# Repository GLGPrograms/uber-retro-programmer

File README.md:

# ÜRP - Über Retro Programmer

An EEPROM programmer for retro playing.
- Can dump most parallel (EE)PROM memories, like 27xxx and 28xxx.
- Supports RW operations of most 28Cxxx EEPROM.
- Suppport may be extended to flash memories up to 1MiB.

## What's inside

This repository is organized as follows
```
ÜRP
 |__ hw          --> KiCAD schematics
 |   |__ gerbers  -> fabrication files (gerbers)
 |   |__ urp.pdf  -> PDF schematic
 |   |__ urp.pro  -> KiCAD project
 |__ fw          --> source code for atmega 328
 |__ sw          --> source code for PC Command Line Interface
 |__ docs        --> files related to documentation
```

After clone, init submodules:
```
git submodule update
````

## PCB Assembly

|Designator      | Description                  | Notes                   |
|----------------|------------------------------|-------------------------|
|C1-C5           | capacitor ceramic 100n P5.08 |                         |
|C6-C7           | capacitor ceramic 22p P2.54  |                         |
|R1              | resistor 10k                 |                         |
|R2-R4           | resistor 330                 |                         |
|Y1              | crystal 16M                  |                         |
|SW1             | Tactile switch               |                         |
|D1-D3           | LED 5mm                      | e.g. green, yellow, red |
|U1              | microcontroller ATMega 328   |                         |
|U2 U3           | shift register 74HC595       |                         |
|JP1-JP5         | 3-pin header 2.54            | EEPROM size selection   |
|J1              | 6-pin header 2.54            |                         |
|J2              | ZIF socket 32 pin wide       |                         |
|J3              | 2-pin header 2.54            | optional                |
|R5              | resistor 10k                 | optional                |
|R6              | resistor 3k3                 | optional                |
|Q1              | PMOS (2N7002)                | optional                |

**Warning:** When Q1 is not mounted, JP7 must be shorted.

## How to compile and load firmware

1. Mount atmega328 on an Arduino UNO board or equivalent. If is a fresh chip, you must load an Arduino compatible bootloader (e.g. optiboot).

1. Compile firmware in `fw` folder using the makefile. Change `/dev/ttyXYZ123` with the correct serial port (e.g. /dev/ttyUSB0);

```
cd fw
make
make program AVRDUDEPORT=/dev/ttyXYZ123
```

1. Move the atmega328 on the ÜRP.

### How to use EEPROM size selection pins

Jumpers JP1-JP6 must be placed according to memory size and technology.
Each jumper has three positions, 1 (green), 2 (red) or unmounted (gray).
Please refer to the following tables for correct placement.

#### EEPROM pinout

#### EPROM pinout

**Notes:**
- EPROM support is read only;
- Most EPROM have VPP on JP2. Datasheet recommends to put VPP=VCC during reading operations. I often keep JP2 in position (1) and make read operations starting from 32768 (A15=VCC).

## How to compile CLI

    cd sw
    make

### CLI options

    Usage: ./serprog options

    -r --read arg                read the content of eeprom in file. Must specify size and addr
    -w --write arg               write the content of file in eeprom, then verify. Must specify addr
    -v --verify arg              verify the content of the file with the eeprom. Must specify addr
    -n --noverify                skip verification after write
    -e --erase                   erase the eeprom (by software, i.e. write FF)
    -V --verbose [arg]           set verbosity level to arg (0 low, 7 high)
    -s --size arg                set reading size
    -a --addr arg                set starting address (default 0)
    -d --device arg              set serial device (default /dev/ttyUSB0)
    -U --unlock                  unlock before
    -P --lock                    lock after
    -h --help                    print this help

#### Read a 28C256 EEPROM (8KiB)

    ./serprog --device /dev/ttyACMx --read dump.bin -s 8192

#### Write a binary image

    ./serprog --device /dev/ttyACMx --write dump.bin

If the EEPROM fails verify, SDP (Software Data Protection) may be on.
Try disabling.

    ./serprog --device /dev/ttyACMx -U --write dump.bin

In both cases, size is deducted from the binary image.

#### Manually verify against a binary image

    ./serprog --device /dev/ttyACMx --verify dump.bin

Size is deducted from the binary image.

#### Protect EEPROM with SDP

    ./serprog --device /dev/ttyACMx -P

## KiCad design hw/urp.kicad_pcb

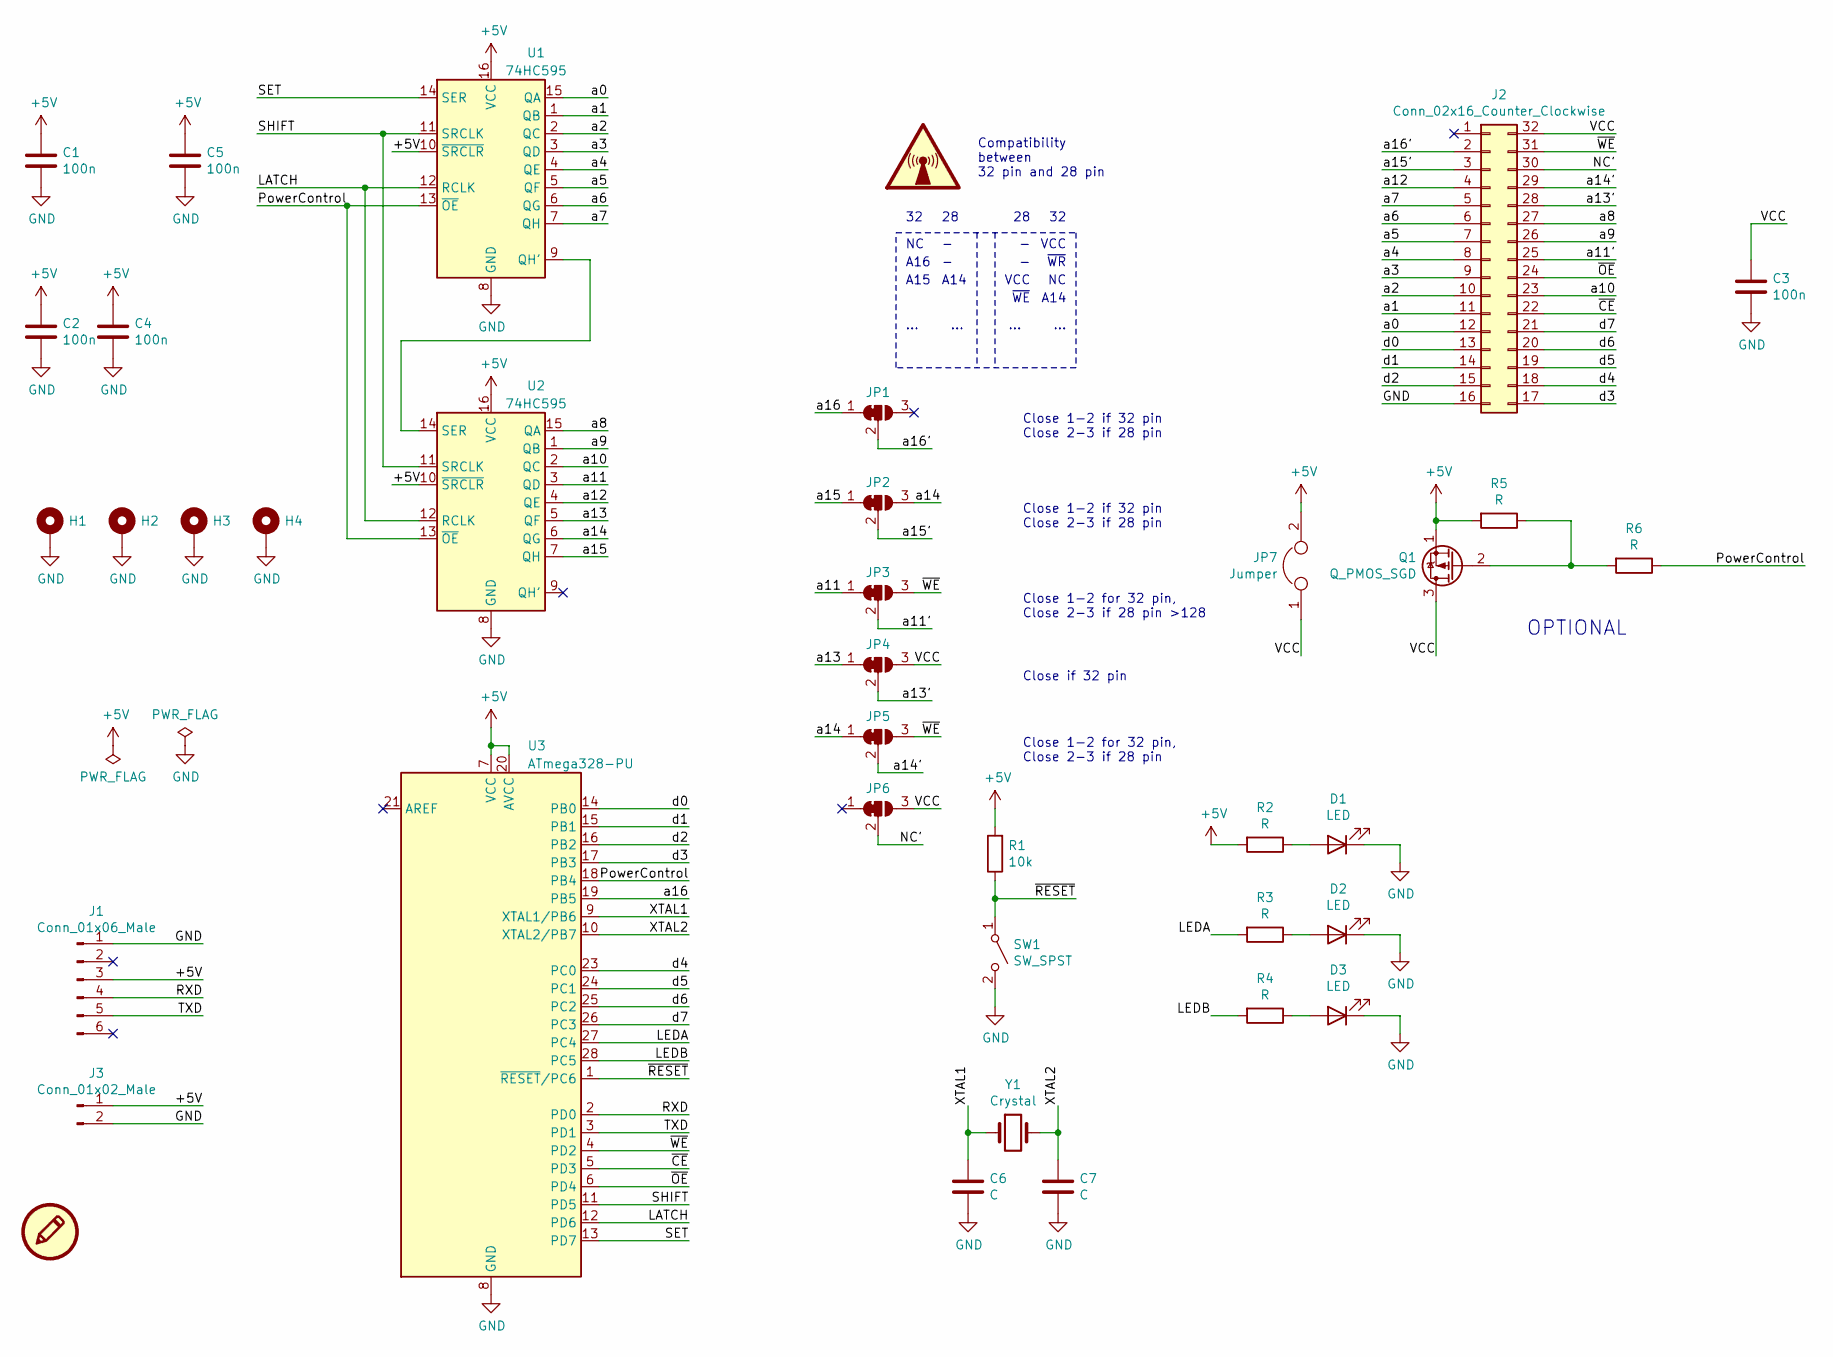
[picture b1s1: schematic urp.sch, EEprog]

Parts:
C1, C2, C3, C4, C5: 100n; C_Disc_D4.7mm_W2.5mm_P5.00mm
C6, C7: C; C_Disc_D3.0mm_W1.6mm_P2.50mm
D1, D2, D3: LED; LED_D5.0mm
H1, H2, H3, H4: MountingHole_Pad; MountingHole_3.2mm_M3_Pad
J1: Conn_01x06_Male; PinHeader_1x06_P2.54mm_Vertical
J2: Conn_02x16_Counter_Clockwise; DIP_Socket-32_W11.9_W12.7_W15.24_W17.78_W18.5_3M_232-1285-0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
J3: Conn_01x02_Male; Molex_KK-254_AE-6410-02A_1x02_P2.54mm_Vertical
JP1, JP2, JP3, JP4, JP5, JP6: SolderJumper_3_Bridged12; PinHeader_1x03_P2.54mm_Vertical
JP7: Jumper; SolderJumper-2_P1.3mm_Open_TrianglePad1.0x1.5mm
Q1: Q_PMOS_SGD; TO-92_Inline
R1: 10k; R_Axial_DIN0204_L3.6mm_D1.6mm_P7.62mm_Horizontal
R2, R3, R4, R5, R6: R; R_Axial_DIN0204_L3.6mm_D1.6mm_P7.62mm_Horizontal
SW1: SW_SPST; SW_PUSH_6mm_H4.3mm
SYM1: GraphicSymbol
U1, U2: 74HC595; DIP-16_W7.62mm_Socket_LongPads
U3: ATmega328-PU; DIP-28_W7.62mm
Y1: Crystal; Crystal_HC49-4H_Vertical

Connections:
+5V: C1.1, C2.1, C4.1, C5.1, J1.3, J3.1, JP7.2, Q1.1 (S), R1.2, R2.2, R5.2, U1.10 (~SRCLR), U1.16 (VCC), U2.10 (~SRCLR), U2.16 (VCC), U3.7 (VCC), U3.20 (AVCC)
/LATCH: U1.12 (RCLK), U2.12 (RCLK), U3.12 (PD6)
/LEDA: R3.2, U3.27 (PC4)
/LEDB: R4.2, U3.28 (PC5)
/NC': J2.30, JP6.2 (C)
/PowerControl: R6.1, U1.13 (~OE), U2.13 (~OE), U3.18 (PB4)
/RXD: J1.4, U3.2 (PD0)
/SET: U1.14 (SER), U3.13 (PD7)
/SHIFT: U1.11 (SRCLK), U2.11 (SRCLK), U3.11 (PD5)
/TXD: J1.5, U3.3 (PD1)
/VCC: C3.1, J2.32, JP4.3 (B), JP6.3 (B), JP7.1, Q1.3 (D)
/XTAL1: C6.1, U3.9 (XTAL1/PB6), Y1.1
/XTAL2: C7.1, U3.10 (XTAL2/PB7), Y1.2
/a0: J2.12, U1.15 (QA)
/a1: J2.11, U1.1 (QB)
/a2: J2.10, U1.2 (QC)
/a3: J2.9, U1.3 (QD)
/a4: J2.8, U1.4 (QE)
/a5: J2.7, U1.5 (QF)
/a6: J2.6, U1.6 (QG)
/a7: J2.5, U1.7 (QH)
/a8: J2.27, U2.15 (QA)
/a9: J2.26, U2.1 (QB)
/a10: J2.23, U2.2 (QC)
/a11: JP3.1 (A), U2.3 (QD)
/a11': J2.25, JP3.2 (C)
/a12: J2.4, U2.4 (QE)
/a13: JP4.1 (A), U2.5 (QF)
/a13': J2.28, JP4.2 (C)
/a14: JP2.3 (B), JP5.1 (A), U2.6 (QG)
/a14': J2.29, JP5.2 (C)
/a15: JP2.1 (A), U2.7 (QH)
/a15': J2.3, JP2.2 (C)
/a16: JP1.1 (A), U3.19 (PB5)
/a16': J2.2, JP1.2 (C)
/d0: J2.13, U3.14 (PB0)
/d1: J2.14, U3.15 (PB1)
/d2: J2.15, U3.16 (PB2)
/d3: J2.17, U3.17 (PB3)
/d4: J2.18, U3.23 (PC0)
/d5: J2.19, U3.24 (PC1)
/d6: J2.20, U3.25 (PC2)
/d7: J2.21, U3.26 (PC3)
/~CE: J2.22, U3.5 (PD3)
/~OE: J2.24, U3.6 (PD4)
/~RESET: R1.1, SW1.1 (A), U3.1 (~RESET~/PC6)
/~WE: J2.31, JP3.3 (B), JP5.3 (B), U3.4 (PD2)
GND: C1.2, C2.2, C3.2, C4.2, C5.2, C6.2, C7.2, D1.1 (K), D2.1 (K), D3.1 (K), H1.1, H2.1, H3.1, H4.1, J1.1, J2.16, J3.2, SW1.2 (B), U1.8 (GND), U2.8 (GND), U3.8 (GND), U3.22 (GND)
unnamed: D1.2 (A), R2.1
unnamed: D2.2 (A), R3.1
unnamed: D3.2 (A), R4.1
unnamed: Q1.2 (G), R5.1, R6.2
unnamed: U1.9 (QH'), U2.14 (SER)

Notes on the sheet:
Compatibility between 32 pin and 28 pin
A16
A15
A14
...
VCC
~WR
~WE
Close 1-2 if 32 pin Close 2-3 if 28 pin
Close 1-2 for 32 pin, Close 2-3 if 28 pin >128
Close if 32 pin
Close 1-2 for 32 pin, Close 2-3 if 28 pin
OPTIONAL

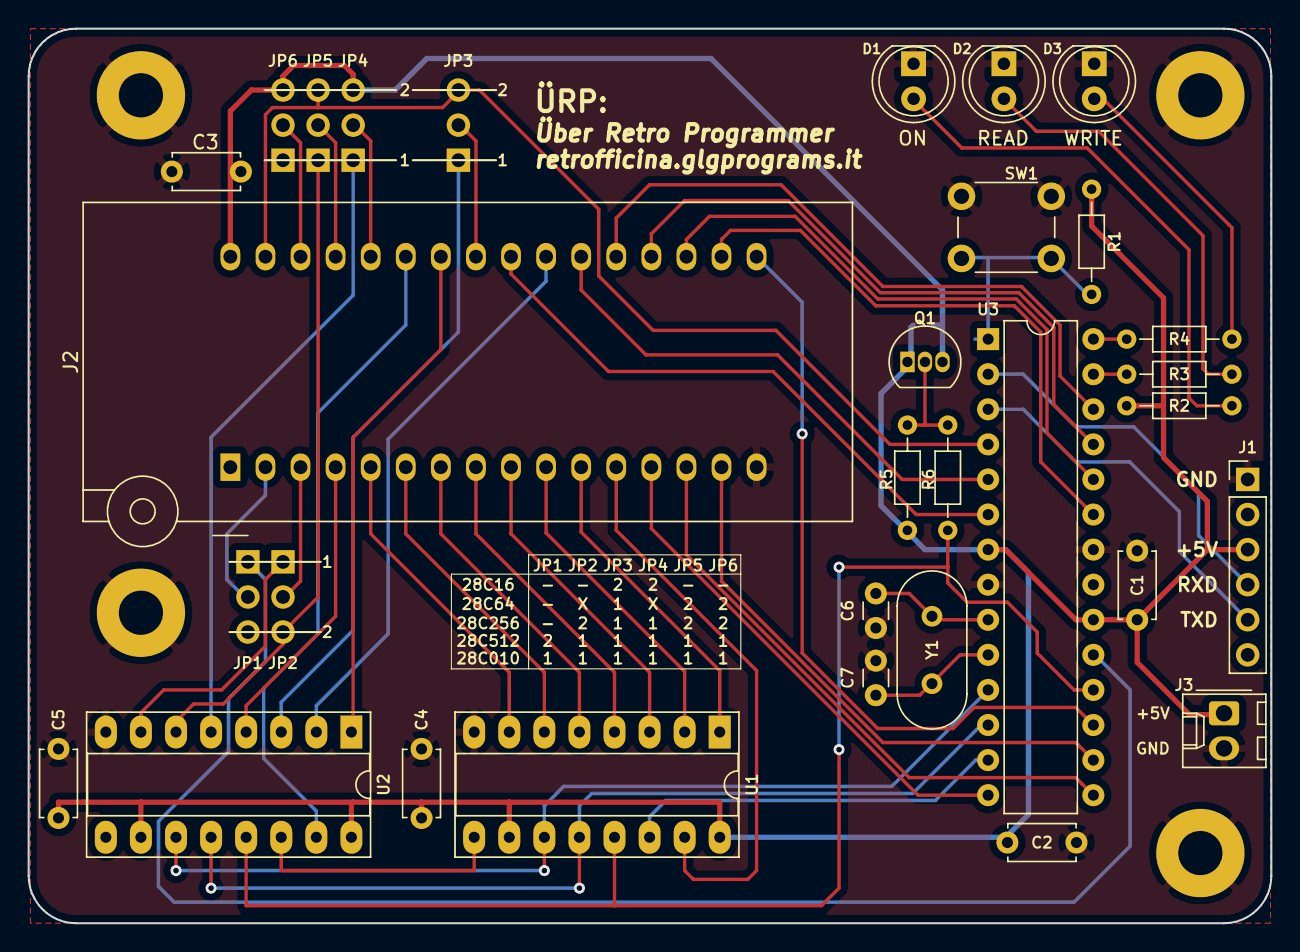
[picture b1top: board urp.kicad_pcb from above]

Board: 2 copper layers, 90.0 x 64.8 mm, 36 parts (1 on the bottom side), 53 nets.

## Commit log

2021-04-10 Fist commit
2021-04-11 [FW] Added submodule libfrser; restored flash_write according to libfrser
2021-04-11 [FW] Custom libfrser (+flash_writen method); Support for RW leds
2021-04-11 [SW] Print read hexdump only if verbose
2021-04-18 [SW] Added help menu
2021-08-20 Pezze per far funzionare sia l'SDP che la scrittura.
    - FIXME: L'sdp funziona per miracolo in ambo i versi facendo una doppia scrittura nell'opbuf.
    - FIXME: La scrittura funziona bene a blocchi (ma quasi sicuramente anche
    sparsa) a patto che si committi l'opbuf ad ogni operazione.
    - La dimensione dell'opbuf è stata portata manualmente a 1024.
    Vale la pena implementare la lettura dello stack per trimmare questo valore.
2021-08-20 Fetch errors count
2021-08-20 Re-Patch: commit opbuf every block
2021-08-20 [SW] Implemented erase
2021-08-20 [SW] compare -> memcmp
2021-08-20 [SW] Added simple makefile
2021-08-20 [docs] updated documentations
2021-10-24 Bugfix in flash write check.
    Now the flash write check is more readable. And maybe really works as
    inteded.
2021-11-07 doc: minor clarifications for repository initialization
2021-11-07 [docs] Added white background to PNG for dark themed preview
2021-11-09 serial port programmer written in rust, first commit
2021-11-09 getopts/parse args from cli
2021-11-10 [sw] fixed erase
2021-11-12 Added gitignore
2021-11-12 read serial baud rate from environment var
2021-11-13 get eeprom programmer name
2021-11-13 get chunk of data from eeprom
2021-11-13 read eeprom and show progress bar
2021-11-14 handle Result of baudrate argument parsing
2021-11-14 read eeprom, possibly with base offset, and save on disk
2021-11-14 write data at address
2021-11-14 write full eeprom, but wait buffer to become empty
    something odd happens: even if ack is received, it messes up if other
    data is sent immediately after, thus a "magic synchronization syscall"
    has been added (thread::sleep)
2021-11-14 [fw] fixed writing for slower roms
    - Longer data polling timeout
    - Plus, fixed typo in data polling value
2021-11-14 receive ack for opbuf_write and opbuf_exec
2021-12-02 rust toolchain 2018 is enough
